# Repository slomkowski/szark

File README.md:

# SZARK

Autonomic robot platform. Work in progress.

## Installation

Requred packages for Ubuntu:
```bash
apt-get install clang cmake git libboost-all-dev libjsoncpp-dev liblog4cpp5-dev libnl-genl-3-dev libnl-route-3-dev libopencv-dev libusb-1.0-0-dev libdw-dev 
```

Steps to clone the repository:
```bash
git clone https://github.com/slomkowski/szark.git
cd szark/
git submodule init
git submodule update
```

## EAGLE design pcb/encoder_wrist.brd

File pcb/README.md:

SZARK - PCBs and schematics
===========================

&copy; 2011 - 2013 Michał Słomkowski GNU GPL v.3
https://github.com/slomkowski/szark

The files here are created in Cadsoft Eagle 6.x Light. You have to have this program installed to open them.

The project contains:
* **bridge** - interface between computer and other robot peripherals,
* **arm_driver**
* **motor_driver**
* **i2c_expander**
* **charger**
* **encoder**, **encoder_se**,**encoder_wrist** - various optical encoder designs installed on power motors and robotic arm.

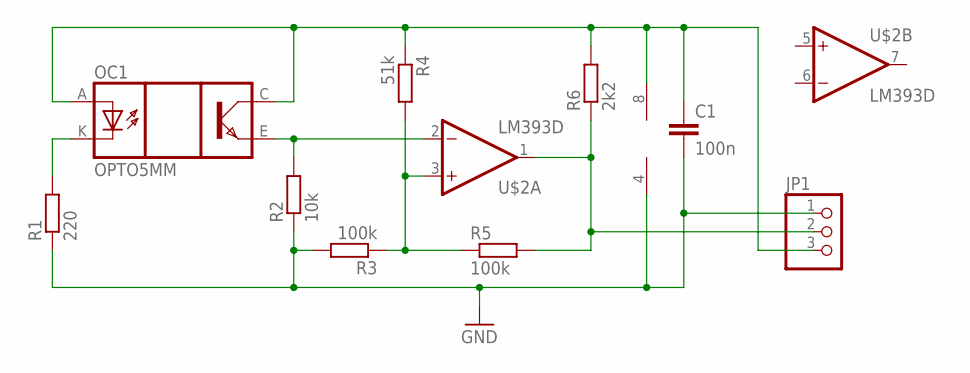
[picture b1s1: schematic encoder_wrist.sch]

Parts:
C1: 100n; C1206
JP1: PINHD-1X3/90; 1X03/90
OC1: OPTO5MM; OPTO_5MM
R1: 220; M1206
R2: 10k; M1206
R3, R5: 100k; M1206
R4: 51k; M1206
R6: 2k2; M1206
U$2: LM393D; SO08

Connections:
GND: C1.2, JP1.1, R1.1, R2.1, R3.2, U$2.4 (V-)
unnamed: OC1.K (C), R1.2
unnamed: R3.1, R4.2, R5.1, U$2.3 (+IN)
unnamed: JP1.2, R5.2, R6.1, U$2.1 (OUT)
unnamed: OC1.E (EMIT), R2.2, U$2.2 (-IN)
unnamed: C1.1, JP1.3, OC1.A, OC1.C (COL), R4.1, R6.2, U$2.8 (V+)

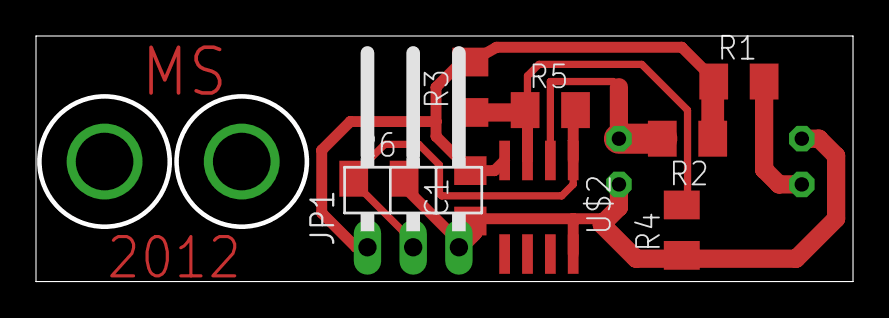
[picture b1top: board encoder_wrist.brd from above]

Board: 2 copper layers, 45.1 x 13.4 mm, 10 parts (1 on the bottom side), 6 nets.

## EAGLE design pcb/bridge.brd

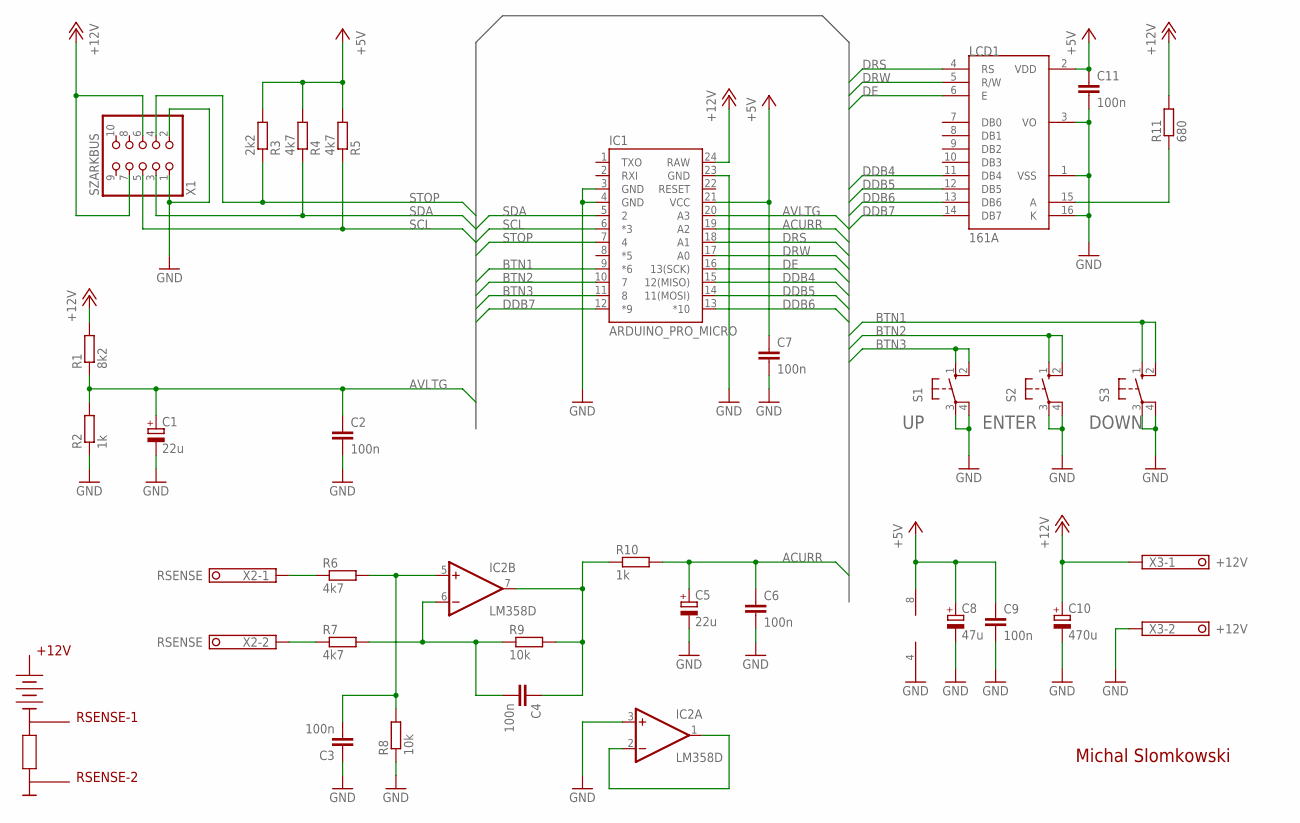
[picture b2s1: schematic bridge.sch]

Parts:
C1, C5: 22u; B/3528-21W
C2, C4, C6, C7, C9, C11: 100n; C1206
C3: 100n; C1210
C8: 47u; C/6032-28W
C10: 470u; E5-8,5
IC1: ARDUINO_PRO_MICRO
IC2: LM358D; SO08
LCD1: 161A
R1: 8k2; M1206
R2, R10: 1k; M1206
R3: 2k2; M1206
R4, R5, R6, R7: 4k7; M1206
R8, R9: 10k; M1206
R11: 680; 0207/12
S1, S2, S3: 10-XX; B3F-10XX
X1: SZARKBUS; 2X05
X2: RSENSE; 1751248
X3: +12V; 1751248

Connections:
+5V: C7.1, C8.+, C9.1, C11.1, IC1.21 (VCC), IC2.8 (V+), LCD1.2 (VDD), R3.2, R4.2, R5.2
+12V: C10.+, IC1.24 (RAW), R1.2, R11.2, X1.6, X1.7, X3.1
ACURR: C5.+, C6.1, IC1.19 (A2), R10.2
AVLTG: C1.+, C2.1, IC1.20 (A3), R1.1, R2.2
BTN1: IC1.9 (*6), S3.1 (S), S3.2 (S1)
BTN2: IC1.10 (7), S2.1 (S), S2.2 (S1)
BTN3: IC1.11 (8), S1.1 (S), S1.2 (S1)
DDB4: IC1.15 (12(MISO)), LCD1.11 (DB4)
DDB5: IC1.14 (11(MOSI)), LCD1.12 (DB5)
DDB6: IC1.13 (*10), LCD1.13 (DB6)
DDB7: IC1.12 (*9), LCD1.14 (DB7)
DE: IC1.16 (13(SCK)), LCD1.6 (E)
DRS: IC1.18 (A1), LCD1.4 (RS)
DRW: IC1.17 (A0), LCD1.5 (R/W)
GND: C1.-, C2.2, C3.1, C5.-, C6.2, C7.2, C8.-, C9.2, C10.-, C11.2, IC1.3 (GND), IC1.4 (GND), IC1.23 (GND), IC2.3 (+IN), IC2.4 (V-), LCD1.1 (VSS), LCD1.3 (VO), LCD1.16 (K), R2.1, R8.1, S1.3, S1.4 (P1), S2.3, S2.4 (P1), S3.3, S3.4 (P1), X1.1, X1.2, X3.2
unnamed: C3.2, IC2.5 (+IN), R6.2, R8.2
unnamed: LCD1.15 (A), R11.1
unnamed: C4.2, IC2.6 (-IN), R7.2, R9.1
unnamed: IC2.1 (OUT), IC2.2 (-IN)
unnamed: R7.1, X2.2
unnamed: R6.1, X2.1
NET3: C4.1, IC2.7 (OUT), R9.2, R10.1
SCL: IC1.6 (*3), R5.1, X1.5
SDA: IC1.5 (2), R4.1, X1.3
STOP: IC1.7 (4), R3.1, X1.4

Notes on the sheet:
+12V
RSENSE-1
RSENSE-2
ENTER
DOWN
Michal Slomkowski

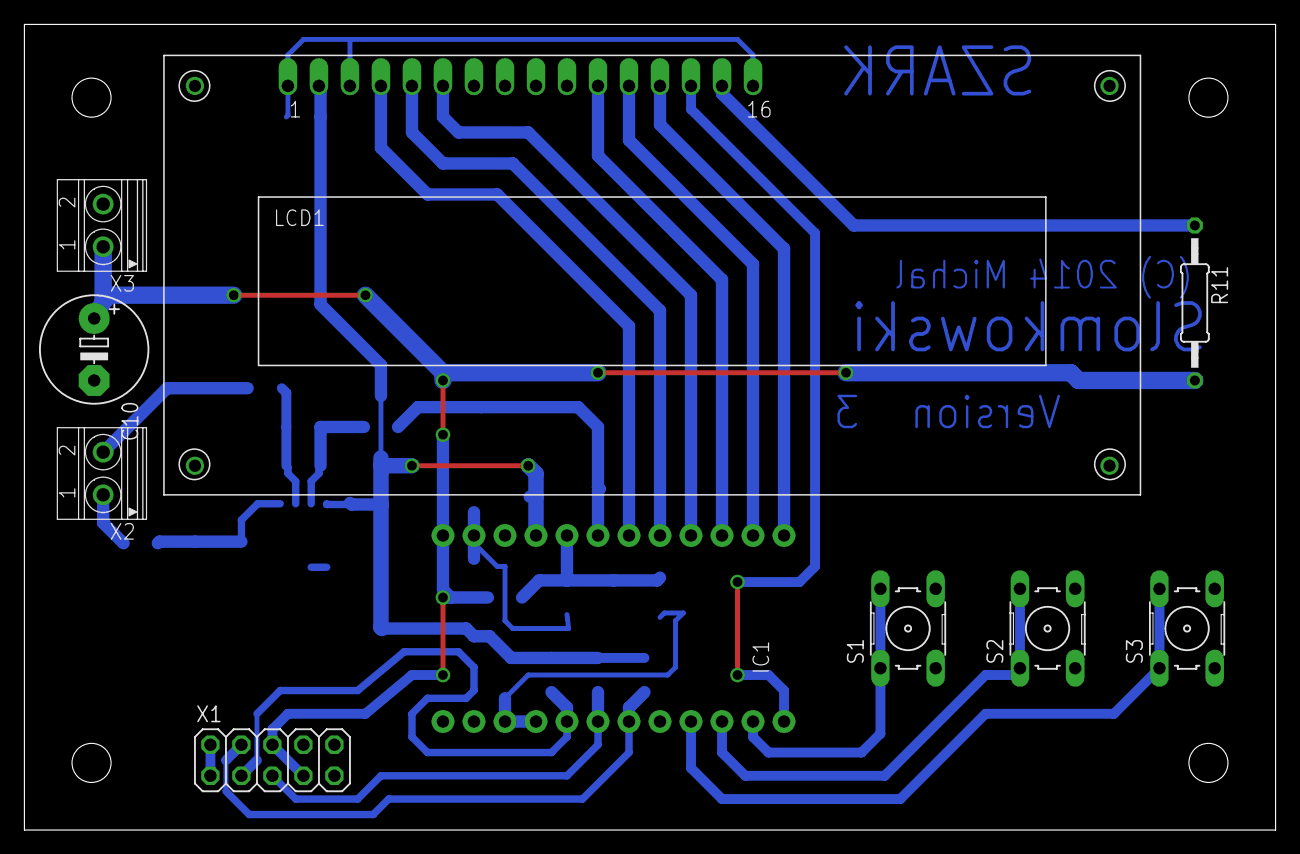
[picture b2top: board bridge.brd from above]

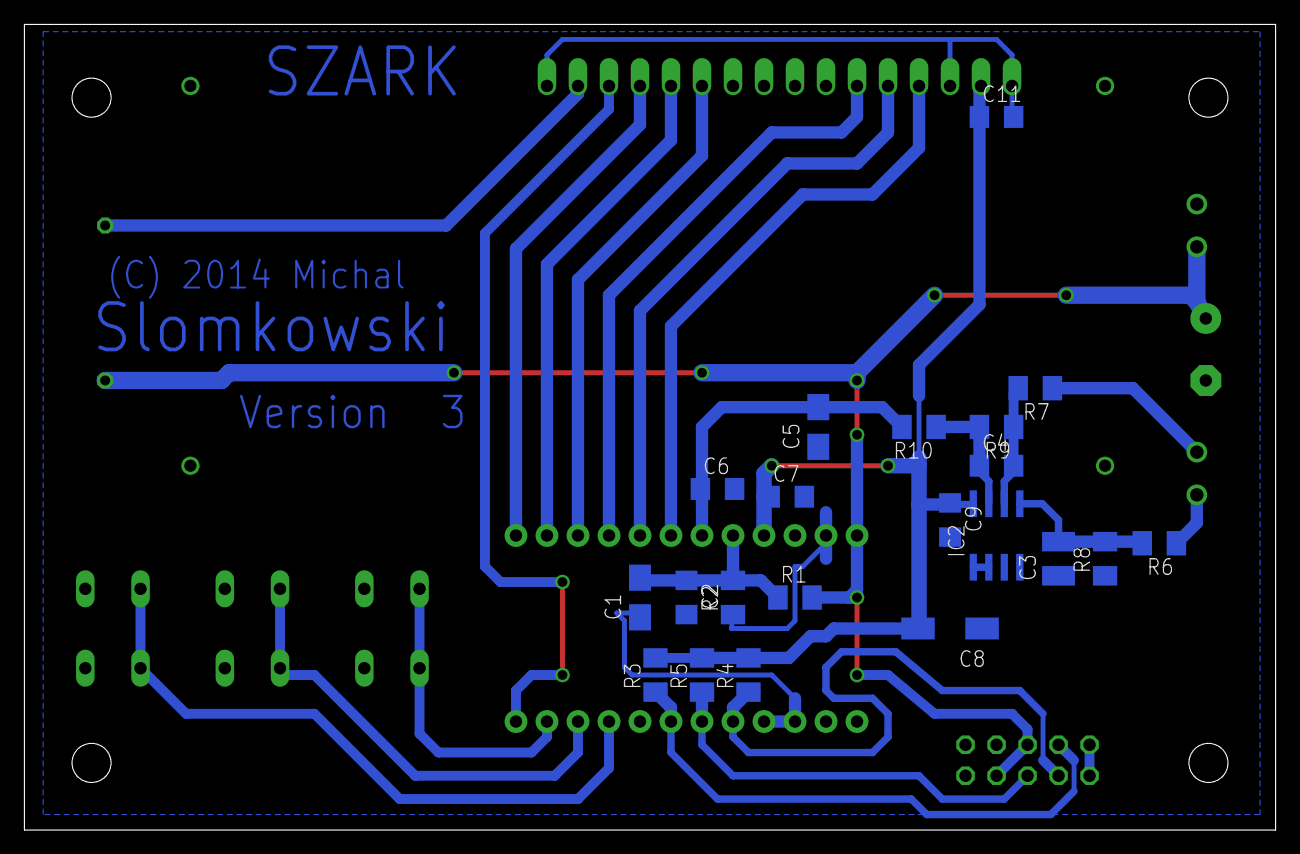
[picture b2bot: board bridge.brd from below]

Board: 2 copper layers, 102.5 x 66.0 mm, 31 parts (21 on the bottom side), 25 nets.

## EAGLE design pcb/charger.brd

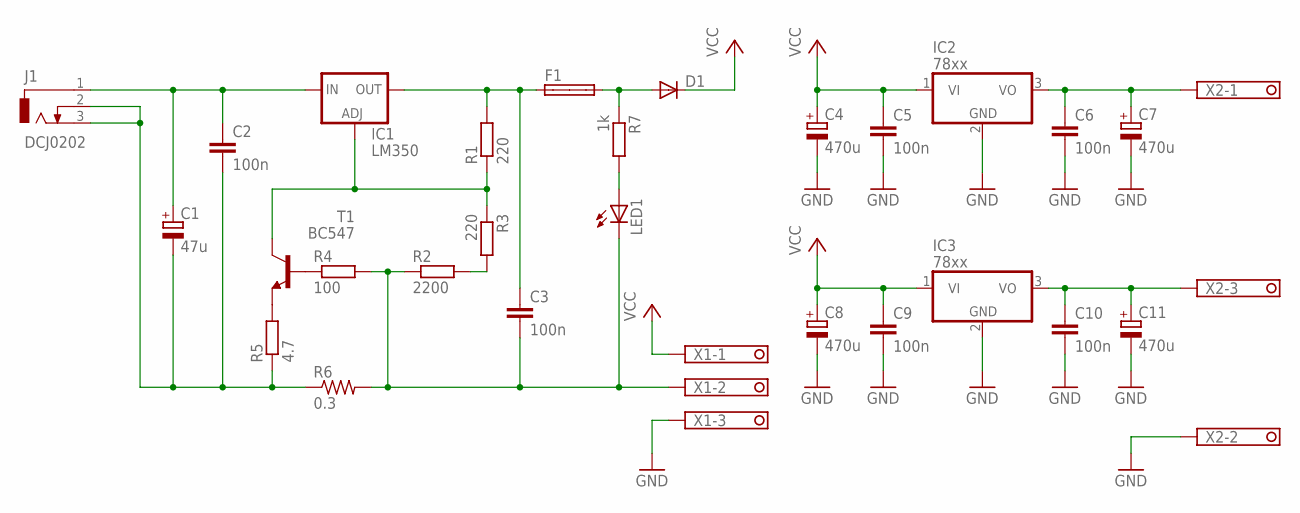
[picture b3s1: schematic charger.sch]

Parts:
C1: 47u; E2,5-7
C2, C3, C5, C6, C9, C10: 100n; C050-030X075
C4, C7, C8, C11: 470u; E5-10,5
D1: SB320; DO201-15
F1: SHK20L
IC1: LM350; 317TS
IC2, IC3: 78xx; TO220V
J1: DCJ0202
LED1: LED5MM
R1, R3: 220; 0207/10
R2: 2200; 0207/10
R4: 100; 0207/10
R5: 4.7; 0207/10
R6: 0.3; 0617/22
R7: 1k; 0207/10
T1: BC547; TO92
X1, X2: 1751251

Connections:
GND: C4.-, C5.2, C6.2, C7.-, C8.-, C9.2, C10.2, C11.-, IC2.2 (GND), IC3.2 (GND), X1.3, X2.2
unnamed: C1.+, C2.1, IC1.3 (IN), J1.1
unnamed: C1.-, C2.2, J1.2, J1.3, R5.1, R6.1
unnamed: R4.1, T1.2 (B)
unnamed: R2.2, R3.2
unnamed: IC1.1 (ADJ), R1.1, R3.1, T1.3 (C)
unnamed: C10.1, C11.+, IC3.3 (VO), X2.3
unnamed: C3.2, LED1.K (C), R2.1, R4.2, R6.2, X1.2
unnamed: R5.2, T1.1 (E)
unnamed: D1.A, F1.2A, R7.1
unnamed: LED1.A, R7.2
unnamed: C6.1, C7.+, IC2.3 (VO), X2.1
unnamed: C3.1, F1.1A, IC1.2 (OUT), R1.2
VCC: C4.+, C5.1, C8.+, C9.1, D1.C, IC2.1 (VI), IC3.1 (VI), X1.1

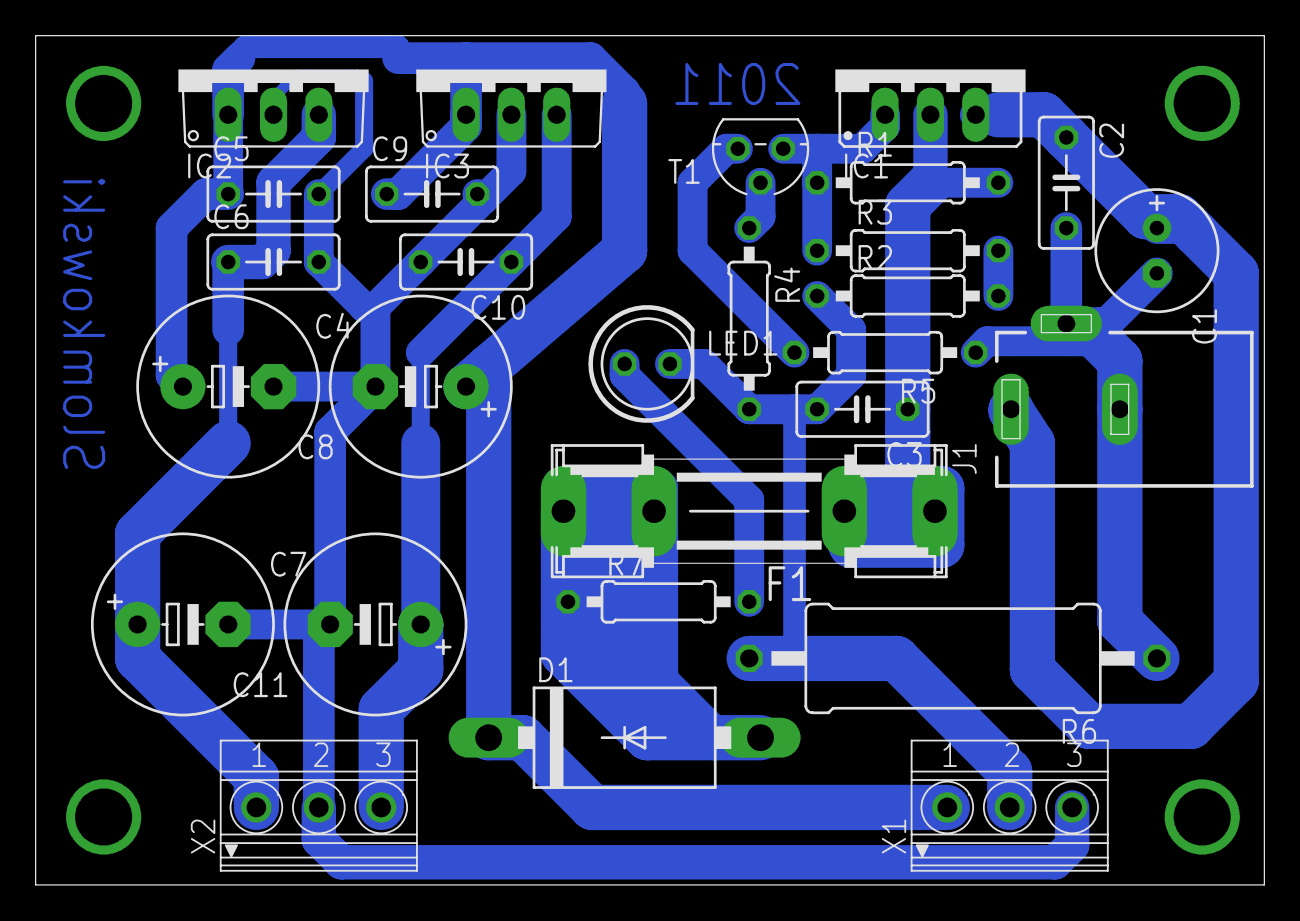
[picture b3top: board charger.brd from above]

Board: 2 copper layers, 68.9 x 47.6 mm, 28 parts (0 on the bottom side), 14 nets.

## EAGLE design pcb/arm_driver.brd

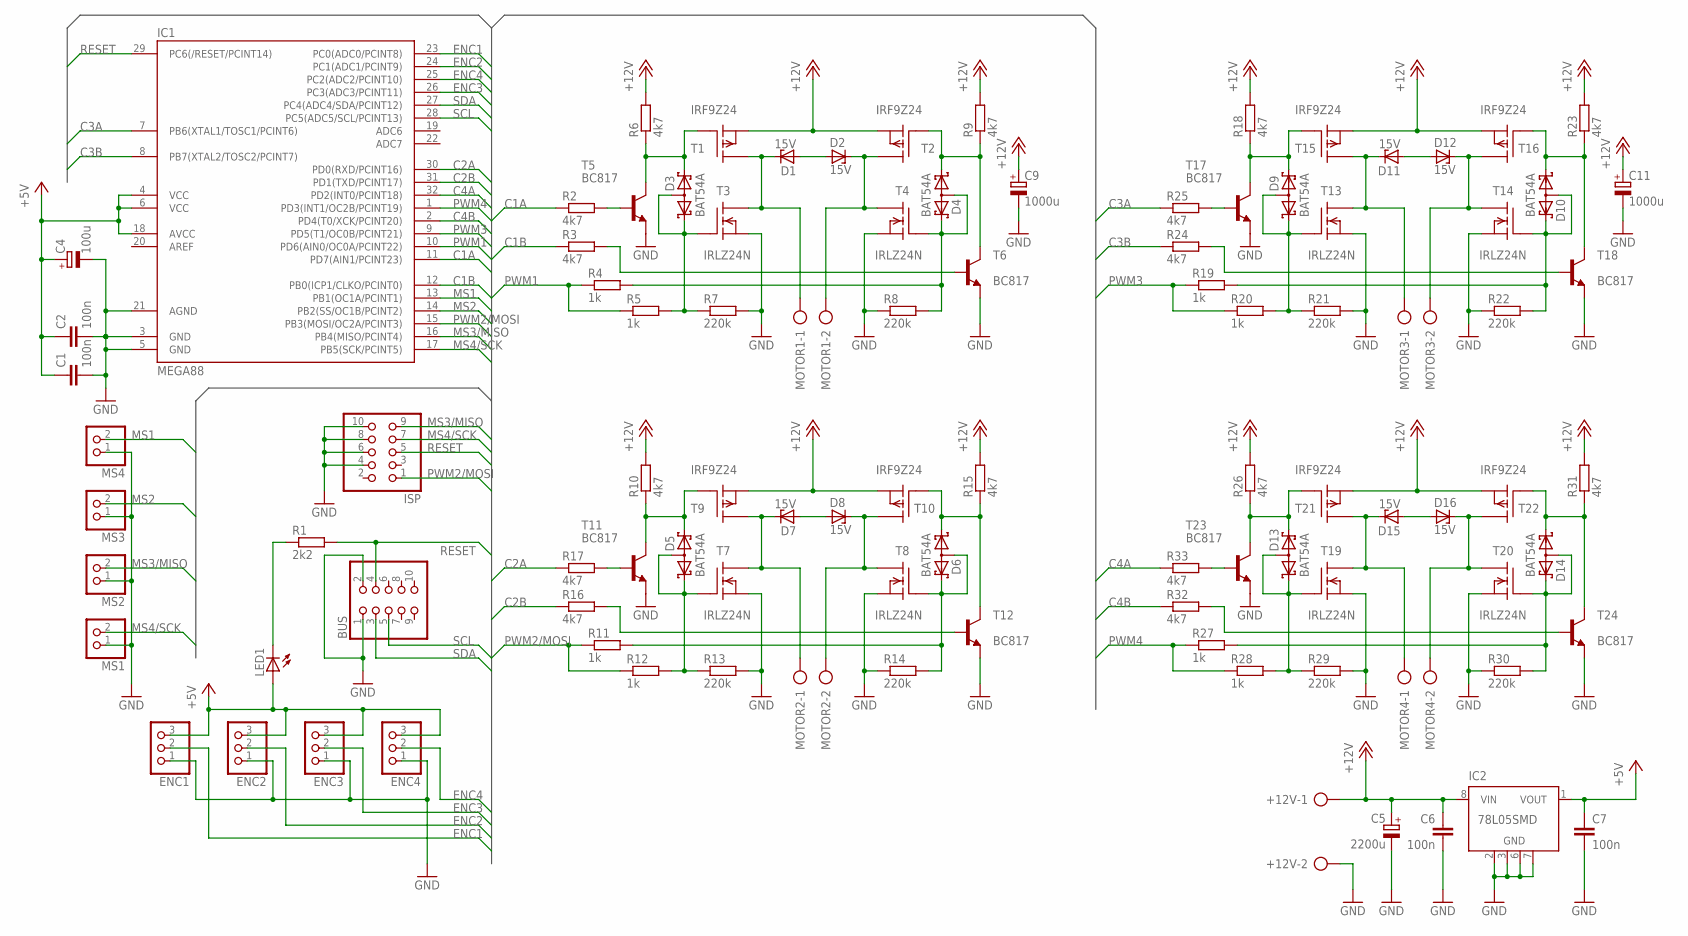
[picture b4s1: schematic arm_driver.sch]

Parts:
+12V: AK500/2
BUS: PINHD-2X5; 2X05
C1, C2, C6, C7: 100n; C1206
C4: 100u; D/7343-31R
C5: 2200u; E7,5-16
C9, C11: 1000u; E5-13
D1, D2, D7, D8, D11, D12, D15, D16: 15V; SOD80C
D3, D4, D5, D6, D9, D10, D13, D14: BAT54A; SOT23
ENC1, ENC2, ENC3, ENC4: PINHD-1X3; 1X03
IC1: MEGA88; TQFP32-08
IC2: 78L05SMD; SO08
ISP: PINHD-2X5; 2X05
LED1: LEDKA-3528ASYC; KA-3528ASYC
MOTOR1, MOTOR2, MOTOR3, MOTOR4: AK500/2
MS1, MS2, MS3, MS4: PINHD-1X2; 1X02
R1: 2k2; R1206
R2, R3, R6, R9, R10, R15, R16, R17, R18, R23, R24, R25, R26, R31, R32, R33: 4k7; R1206
R4, R5, R11, R12, R19, R20, R27, R28: 1k; R1206
R7, R8, R13, R14, R21, R22, R29, R30: 220k; R1206
T1, T2, T9, T10, T15, T16, T21, T22: IRF9Z24; TO220
T3, T4, T7, T8, T13, T14, T19, T20: IRLZ24N; TO220
T5, T6, T11, T12, T17, T18, T23, T24: BC817; SOT23-BEC

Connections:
+5V: C1.1, C2.1, C4.+, C7.1, ENC1.3, ENC2.3, ENC3.3, ENC4.3, IC1.4 (VCC), IC1.6 (VCC), IC1.18 (AVCC), IC2.1 (VOUT), LED1.A
+12V: +12V.1, C5.+, C6.1, C9.+, C11.+, IC2.8 (VIN), R6.2, R9.2, R10.2, R15.2, R18.2, R23.2, R26.2, R31.2, T1.3 (S), T2.3 (S), T9.3 (S), T10.3 (S), T15.3 (S), T16.3 (S), T21.3 (S), T22.3 (S)
C1A: IC1.11 (PD7(AIN1/PCINT23)), R2.1
C1B: IC1.12 (PB0(ICP1/CLKO/PCINT0)), R3.1
C2A: IC1.30 (PD0(RXD/PCINT16)), R17.1
C2B: IC1.31 (PD1(TXD/PCINT17)), R16.1
C3A: IC1.7 (PB6(XTAL1/TOSC1/PCINT6)), R25.1
C3B: IC1.8 (PB7(XTAL2/TOSC2/PCINT7)), R24.1
C4A: IC1.32 (PD2(INT0/PCINT18)), R33.1
C4B: IC1.2 (PD4(T0/XCK/PCINT20)), R32.1
ENC1: ENC1.2, IC1.23 (PC0(ADC0/PCINT8))
ENC2: ENC2.2, IC1.24 (PC1(ADC1/PCINT9))
ENC3: ENC3.2, IC1.26 (PC3(ADC3/PCINT11))
ENC4: ENC4.2, IC1.25 (PC2(ADC2/PCINT10))
GND: +12V.2, BUS.1, BUS.2, C1.2, C2.2, C4.-, C5.-, C6.2, C7.2, C9.-, C11.-, ENC1.1, ENC2.1, ENC3.1, ENC4.1, IC1.3 (GND), IC1.5 (GND), IC1.21 (AGND), IC2.2 (GND), IC2.3 (GND), IC2.6 (GND), IC2.7 (GND), ISP.4, ISP.6, ISP.8, ISP.10, MS1.1, MS2.1, MS3.1, MS4.1, R7.2, R8.1, R13.2, R14.1, R21.2, R22.1, R29.2, R30.1, T3.3 (S), T4.3 (S), T5.E, T6.E, T7.3 (S), T8.3 (S), T11.E, T12.E, T13.3 (S), T14.3 (S), T17.E, T18.E, T19.3 (S), T20.3 (S), T23.E, T24.E
MS1: IC1.13 (PB1(OC1A/PCINT1)), MS4.2
MS2: IC1.14 (PB2(SS/OC1B/PCINT2)), MS3.2
MS3/MISO: IC1.16 (PB4(MISO/PCINT4)), ISP.9, MS2.2
MS4/SCK: IC1.17 (PB5(SCK/PCINT5)), ISP.7, MS1.2
unnamed: LED1.C, R1.1
unnamed: D2.C, MOTOR1.2, T2.2 (D), T4.2 (D)
unnamed: D1.A, D2.A
unnamed: D3.2 (K2), R6.1, T1.1 (G), T5.C
unnamed: D4.1 (K1), R9.1, T2.1 (G), T6.C
unnamed: D4.2 (K2), D4.3 (AA), R4.2, R8.2, T4.1 (G)
unnamed: R3.2, T6.B
unnamed: R2.2, T5.B
unnamed: D3.1 (K1), D3.3 (AA), R5.2, R7.1, T3.1 (G)
unnamed: D1.C, MOTOR1.1, T1.2 (D), T3.2 (D)
unnamed: D7.C, MOTOR2.1, T7.2 (D), T9.2 (D)
unnamed: D8.C, MOTOR2.2, T8.2 (D), T10.2 (D)
unnamed: D5.2 (K2), R10.1, T9.1 (G), T11.C
unnamed: D6.1 (K1), R15.1, T10.1 (G), T12.C
unnamed: D6.2 (K2), D6.3 (AA), R11.2, R14.2, T8.1 (G)
unnamed: D5.1 (K1), D5.3 (AA), R12.2, R13.1, T7.1 (G)
unnamed: D7.A, D8.A
unnamed: R16.2, T12.B
unnamed: R17.2, T11.B
unnamed: D11.C, MOTOR3.1, T13.2 (D), T15.2 (D)
unnamed: D12.C, MOTOR3.2, T14.2 (D), T16.2 (D)
unnamed: D9.2 (K2), R18.1, T15.1 (G), T17.C
unnamed: D10.1 (K1), R23.1, T16.1 (G), T18.C
unnamed: D10.2 (K2), D10.3 (AA), R19.2, R22.2, T14.1 (G)
unnamed: D9.1 (K1), D9.3 (AA), R20.2, R21.1, T13.1 (G)
unnamed: D11.A, D12.A
unnamed: R24.2, T18.B
unnamed: R25.2, T17.B
unnamed: D15.C, MOTOR4.1, T19.2 (D), T21.2 (D)
unnamed: D16.C, MOTOR4.2, T20.2 (D), T22.2 (D)
unnamed: D13.2 (K2), R26.1, T21.1 (G), T23.C
unnamed: D14.1 (K1), R31.1, T22.1 (G), T24.C
unnamed: D14.2 (K2), D14.3 (AA), R27.2, R30.2, T20.1 (G)
unnamed: D13.1 (K1), D13.3 (AA), R28.2, R29.1, T19.1 (G)
unnamed: D15.A, D16.A
unnamed: R32.2, T24.B
unnamed: R33.2, T23.B
PWM1: IC1.10 (PD6(AIN0/OC0A/PCINT22)), R4.1, R5.1
PWM2/MOSI: IC1.15 (PB3(MOSI/OC2A/PCINT3)), ISP.1, R11.1, R12.1
PWM3: IC1.9 (PD5(T1/OC0B/PCINT21)), R19.1, R20.1
PWM4: IC1.1 (PD3(INT1/OC2B/PCINT19)), R27.1, R28.1
RESET: BUS.4, IC1.29 (PC6(/RESET/PCINT14)), ISP.5, R1.2
SCL: BUS.5, IC1.28 (PC5(ADC5/SCL/PCINT13))
SDA: BUS.3, IC1.27 (PC4(ADC4/SDA/PCINT12))

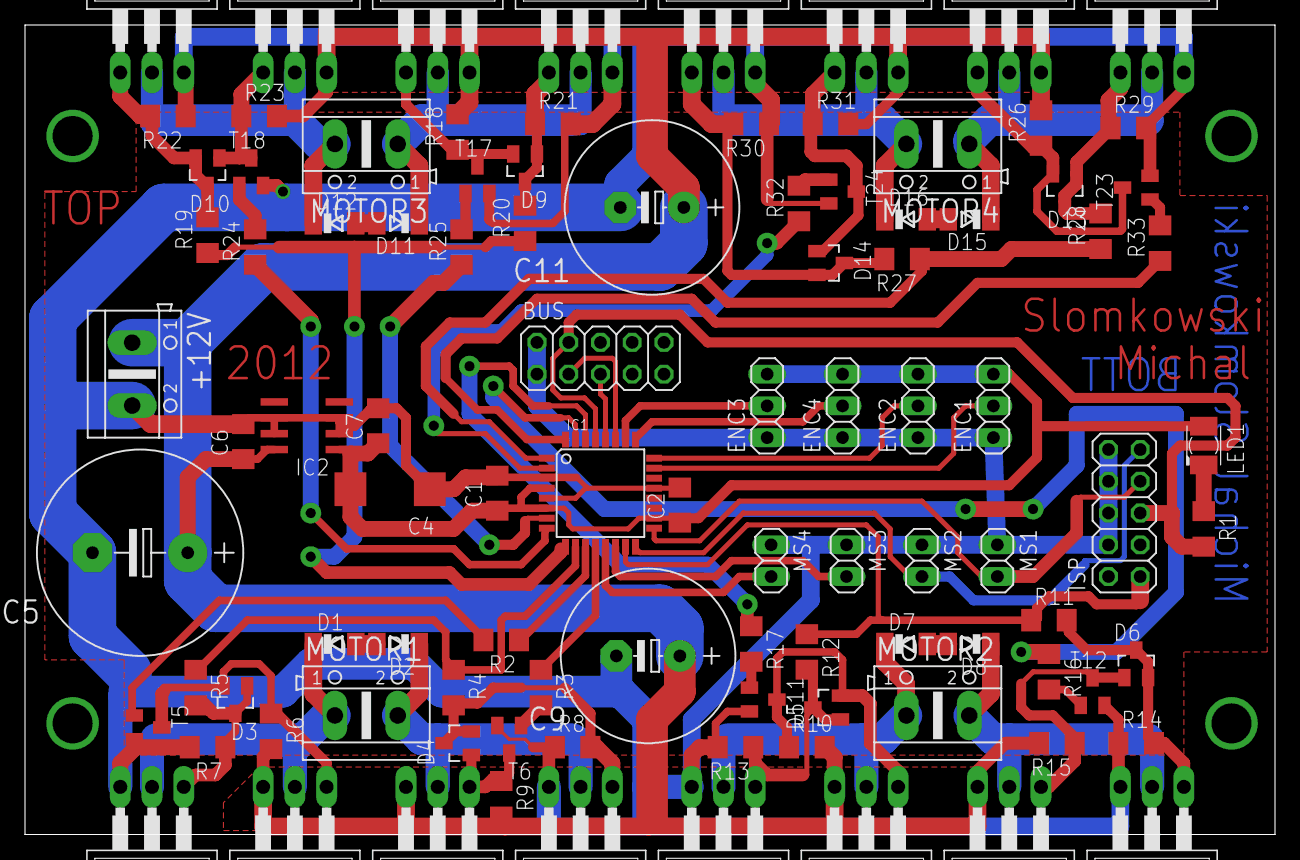
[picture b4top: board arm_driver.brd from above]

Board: 2 copper layers, 100.0 x 64.8 mm, 99 parts (0 on the bottom side), 63 nets.

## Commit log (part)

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2013-07-16 Added datasheets.
2013-07-16 Motor driver project added.
2013-07-17 Changed common firmware files.
2013-07-18 Bridge firmware added.
2013-07-18 Bridge converted to C++.
2013-07-21 Displaying speed in motor driver menu.
2013-07-22 PCB boards and schematics upload.
2013-07-22 Further refactoring.
2013-07-23 Bridge USB schematic.
2013-07-28 Bridge board ready.
2013-07-29 Added arm_driver project.
2013-07-29 Fix name 'callibrate' to 'calibrate'
2013-07-30 Arm_driver added namespaces and name refactor. Code size 3374 B.
2013-07-30 Eliminated C++ warnings. No further refactor - code is too magical.
2013-07-30 Adjusted bridge to use new enum interface for motor and arm.
2013-07-31 arm_driver increased calibrate speed for elbow.
2013-07-31 Added V-USB library to bridge.
2013-08-05 Raw working USB HID example from V-USB.
2013-08-05 bridge: Added I2C driver and part of motor_driver.
2013-08-05 Deleted eagle.epf.
2013-08-06 Analog added.
2013-08-06 Added full interface to motor_driver.
2013-08-06 Added arm_driver.
2013-08-06 Added I2C expander interface.
2013-08-07 Deleted eagle.epf
2013-08-07 Added menu skeleton.
2013-08-08 I2C expander menu support.
2013-08-08 Added actual speed display to motor driver menu.
2013-08-08 Moved menu class generic code to separate file.
2013-08-08 Updated names from MOTOR_X to X.
2013-08-09 Corrected bridge voltage divider to match the resistor values.
2013-08-10 Slightly changed LCD procedures.
2013-08-10 Added interrupt routine to kill switch to hold down active state and modified the operation to open collector mode.
2013-08-10 Fixed LCD init procedure.
2013-08-11 Fixed wrong interrupt number.
2013-08-11 Moved all protocol definitions in arm from defines to enums.
2013-08-11 Added kill switch support to menu.
2013-08-11 Updated waiting times and replaced custom waiting functions with _delay_ms in initialization functions.
2013-08-12 Moved USB request function to separate files.
2013-08-13 Added option to read buttons state without debouncing (no delay).
2013-08-17 Updated LCD functions to limit characters.
2013-08-18 arm and motor get.
2013-08-18 Added empty class to create bridge interface on the host side.
2013-08-19 Parts of implementation of bridge, only for bridge.
2013-08-21 Added DataHolder class to hold requests. Changed arm, expander and motor classes to hold the pointer to Interface in order to use Implementation struct. Added some crazy reference initialization list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
2013-08-21 Implemented motor interface setters.
2013-08-22 Added arm interface to host.
2013-08-22 Added motor set and arm set to bridge.
2013-08-23 Fixed usb request.
2013-08-24 Extracted class InterfaceManager.
2013-08-24 Finished getters and listeners, control should be performed by InterfaceManager.
2013-08-24 Bridge support interrupt transfer to host.
2013-08-26 I2C timer - stopping counting after successful receivement.
2013-08-28 Changed fusebits to start immadently after activation (without 65 ms delay).
2013-08-28 Bridge - backed to control transfers, beta works.
2013-08-29 Corrected receiver funcion in bridge.
2014-03-06 Add Sparkfun library and ATMEGA32U4 datasheet.
2014-03-07 bridge: Update schematic positions and numbering.
2014-03-10 bridge: board shape.
2014-03-13 bridge: Board ready beta.
2014-03-16 bridge: Update resistor values.
2014-03-16 bridge: Change pinouts in firmware to match the new hardware.
2014-03-17 bridge: Adjust firmware to run on the new board.
    Makefile adjusted to program with AVRDoper.
2014-03-17 bridge: Modify LCD support to read busy flag.
2014-03-17 Fix common header references from .h to .hpp
2014-03-18 Change .h to .hpp in arm_driver and motor_driver.
2014-03-18 bridge: Add software reset when UP+DOWN buttons.
2014-03-18 Add bridge bootloader code basing on CDC bootloader from LUFA.
2014-03-18 Gitignore update.
2014-03-18 bridge: Add LUFA builder.
2014-03-18 bridge: Add LED support.
2014-03-21 bridge: Add LUFA USB communication with bulk transfers.
2014-03-21 server: Working communication over bulk transfers.
    Slow.
2014-03-22 Send packet with the fixed size of 128 bytes. Fast.
2014-03-22 bridge: Slight refactor. Change endpoint numbers.
2014-03-22 server: Add log4cpp support. USBCommunicator and InterfaceManager logging.
2014-03-22 bridge: Add version submenu.
2014-03-23 server: Add Scons build system scripts.
2014-03-23 server: Deleted Eclipse files.
2014-04-06 server: Add logger.properties file.
2014-04-06 Updated .gitignore and change permissions.
2014-04-24 server: Add Configuration class with test.
2014-04-26 server: Update code formatting and namespaces.
2014-04-26 Move all external libraries to external-libs/ directory.
2014-04-26 server: Dependency name fix and change sleep() to sleep_for().
2014-04-27 Clean up, remove residual Eclipse project files.
2014-04-27 server: Add BridgeProcessor class with test.
2014-04-27 server: Remove USBCommunicator dependency from InterfaceManager (call lambda for sync).
2014-04-27 server: Add response generation to BridgeProcessor.
2014-04-28 server: Add killswitch to BridgeProcessor among with hardware killswitch info to Interface.
2014-04-28 bridge: Fix info about hardware killswitch.
2014-04-28 bridge: Add filling the output buffer with MESSAGE_END;
2014-05-01 server: Add request creator template to BridgeProcessor.
2014-05-08 server: Change addRequest in RequestQueuer to return the ID of the accepted request.
2014-05-08 Add shell script to update external libs.
    You have to execute:
    ./update_external_libs.sh
    to clone repositories or pull if they exist.
2014-05-08 Add SZARK client project.
    Add Maven script. Modify icon paths to use getResource(). Project compiles and runs, but cannot load Jinput library for Linux
    (joystick).
2014-05-08 client: Clean up all source files.
2014-05-08 server: Fix naming in generated JSON.
2014-05-08 server: Fix NetServer sendersMap accesses to be thread-safe.
2014-05-10 server: Fix mutex in BridgeProcessor, add log notice when maintenance task, fix NetServer broken references to endpoint in async send.
2014-05-10 server: Add logging to Interface class.
2014-05-10 server: Fix order in requests queue + some logger messagess.
2014-05-10 client: Add annotations for expander status.
2014-05-10 Add Python scripts usable for various testing.
    Added two scripts:
    * send 'get status' request to the bridge via USB
    * send many UDP packets with JSON to the server
2014-05-13 server: Add priorities to the bridge requests.
2014-05-13 sever: Add requests ordering with priority.
2014-05-14 server: Fix loosing settings for motor (double command).
2014-05-14 server: Same fix for arm.
2014-09-21 server: Add CMake build script and update gitignore.
2014-09-21 server: Remove Scons build file.
2014-09-26 bridge: Remove wrist from menu.
2014-09-26 client: Add receiving JSON.
2014-09-26 client: Add support of kill switch.
2014-09-26 server: Remove library build from CMake. Update gitignore + logger properties.
2014-09-27 szarkcam: Add new project for image capture.
2014-09-27 szarkcam: Add rotation.
2014-09-28 client: Add new camera updater support.
2014-09-28 client: Add switching between RAW and HUD modes.
2014-09-29 client: Add disabling camera when error occurred.
2014-09-29 client: Refactor HardcodedConfiguration and extract max speed settings as variable.
2014-09-29 client: Refactor joystick.
2014-09-29 server: Fix removal of rejected requests when overflow.
2014-09-29 Update send_requests script.
2014-09-30 client: Remove lock from Status.
2014-10-01 client: Add timeouts to sockets and fix error with hanging.
2014-10-03 client: Add calibration support.
2014-10-03 client: Add SwingWorker for connection.
2014-10-08 szarkcam: Dummy project structure for VIPS.
2014-10-08 server: Add calibration support (ALPHA).
2014-10-08 szarkcam: Add grabbing from OpenCV.
2014-10-09 szarkcam: Add automatic detection of faster camera.
2014-10-10 szarkcam: Refactor.
2014-10-10 szarkcam: Add HUD drawing stub.
2014-10-11 szarkcam: Fix proper rotation.
2014-10-11 client: Add SwingWorker to Disconnect button.
2014-10-12 client: Arm visualizer draws shoulder and elbow.
2014-10-12 client: Arm visualizer add drawing robot base.
2014-10-14 server: Update voltage and current factors.
2014-10-14 arm: Fix random data after calibration.
2014-10-18 Add common server library.
2014-10-18 camera: Adjust project to use common lib.
2014-10-18 server: Fix tests to compile.
2014-10-19 common: Add base for color logging.
2014-10-19 Change servers to use initializeProgram().
2014-10-19 common: Add color log support.
2014-10-20 server: Add passing client IP address to processors.
2014-10-20 client: Add Wi-Fi strength support.
2014-10-20 server: Change to use INI file format.
2014-10-20 camera: Update to use INI file.
2014-10-20 server: Move convert functions to separate file, use instance logger for Interface.
2014-10-21 server: Convert InterfaceManager to DI object.
2014-10-22 server: Move Interface to common lib and allocate memory for it in SHM.
2014-10-22 server: Add names to threads.
2014-10-23 server: Copy bitrate and strength code.
2014-10-25 server: Fix tests for WifiInfo.
2014-10-25 server: Add code for grabbing ARP table.
2014-10-25 server: Change ARP implementation to use libnl.
2014-10-25 server: Fix compilation for GCC.
2014-10-25 client: Fix Wi-Fi strength bar.
2015-11-30 Add implementation of new pad backend for Xbox 360 pad.
2015-12-08 common: Fix tests to make them compile.
2015-12-08 camera: Fix tests to make them compile. Add head camera classes.
2015-12-08 camera: Reformat CMakeLists.txt to create static library.
    * reformat all code
    * clean up headers and header guards
2015-12-09 camera: Add TurboJpegEncoder.
2015-12-12 camera: Add Video4Linux image grabber.
2015-12-13 camera: Fix and refactor frame grabber in V4L.
2015-12-13 Add PixFc library.
2015-12-15 server: Add managed mode in WifiInfo.
2015-12-17 server: Add zeroing request queue after request 0.
2015-12-18 server: Reformat all source files.
2015-12-19 common: Clean all source files.
2015-12-19 server: Remove boost::format from logger calls.
2015-12-20 camera: Add motor speed bars to head HUD.
2015-12-20 Refactor shared memory code to common lib.
2015-12-22 Add timestamp to the Status.
2016-01-03 Replace RequestMap in Interface with boost::interprocess:map. Add crude test to shared Interface.
2016-01-05 Add interprocess mutex to Interface.
2016-01-05 camera: Set better struct initialization. common: Add better test for shared interface.
2016-01-06 Update README.
2016-01-19 client: Add JAR loader.
2016-01-19 camera: Add JSON params support.
2016-01-19 Update viewer script.
2016-01-19 server: Change WifiInfo to get IPv6 addresses from ARP.
2016-02-06 server: Replace JSON response generator with minijson_writer.
2016-02-06 Bumb Wallaroo to 0.7.
2016-02-06 server: Bumb wallaroo to 0.7.
2016-02-07 server: Fix 03 crash and add some optimizations.
2016-02-11 Fix SharedInterfaceProvider destructor error. Fix logger name typos.
2016-02-13 Fix CMake files to include PKG libraries as well.
2016-02-13 Move threadSetName to common llib.
2016-02-13 client: Add JPEG quality support.
2016-02-13 client: Migrate to logback.
2016-02-13 client: Add support for camera timestamps.
2016-02-13 Add supervisord script.
2016-03-01 server: Add first version with RapidJSON.
2016-03-02 server: Shorten identifications in json.
2016-03-02 common: Optimize convert functions.
2016-03-04 common: Add write option to Configuration.
2016-03-04 camera: Update CameraImageGrabberTest.
2016-03-04 camera: Add save feature to tests.
2016-04-11 camera: Add video input support and dynamic flip.
2016-04-13 Move configs to example.config.
2016-04-13 Move image receiver to utils directory. Add simple query script.
2016-04-13 camera: Fix NetworkServer types.
2016-06-25 server: Move config files to example.
2025-10-21 server: Update code to match up-to-date libraries.

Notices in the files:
pcb/bridge.brd:
(C) 2014 Michal
parts and their libraries:
sparkfun-boards: Licensing: Creative Commons ShareAlike 4.0 International - https://creativecommons.org/licenses/by-sa/4.0
